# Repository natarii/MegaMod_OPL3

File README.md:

# OPL3 MegaMod
This add-on board lets you play OPL, OPL2, and OPL3 VGM files using your MegaGRRL Desktop.

**This board is provided as an experimental add-on. Software support is working, but incomplete. Software support may improve in the future.**

**MegaGRRL Desktop Firmware v0.97dev or newer is required!** See [Firmware Releases](https://git.agiri.ninja/natalie/megagrrl/-/releases)

## Usage
1. Power off the MegaGRRL Desktop.
2. Remove the YM2612 and SN76489, and seat the addon board into their sockets.
3. Set all 4 DIP switches on the desktop board to OFF.
4. Power on. The presence of the OPL3 board will be detected upon boot. Play an OPL/OPL2/OPL3 VGM file.

## Bill of Materials
| Ref.Dsg. | Value | 
| -------- | ----- |
| C1 | 10uF electrolytic |
| C2 | 47pF ceramic |
| C3 | 2.7nF ceramic |
| C4 | 2.7nF ceramic |
| C5 | 0.1uF ceramic |
| C6 | 0.1uF ceramic |
| C7 | 0.1uF ceramic |
| R1 | 33 ohm |
| R2 | 1k ohm |
| IC1 | YMF262 aka YMF262-M (SMD) |
| IC2 | YAC512 (SMD) |
| IC3 | TL072 (THT) (or SA5532, many opamps will work) |
| D1 | 1N5819 |
| Misc | 0.1" machine pin male-to-male headers, 40 pins total required. Must be machine pin type!!! |

All capacitors, resistors, diode are THT

## Assembly
1. Solder on the SMD components (YMF262, YAC512)
2. Solder on the THT components (SA5532, capacitors, resistors, diode)
3. Solder on the pin headers (use MegaGRRL Desktop IC sockets for alignment)

## Gerber files
Gerbers for JLCPCB are in the `gerbers/` directory.

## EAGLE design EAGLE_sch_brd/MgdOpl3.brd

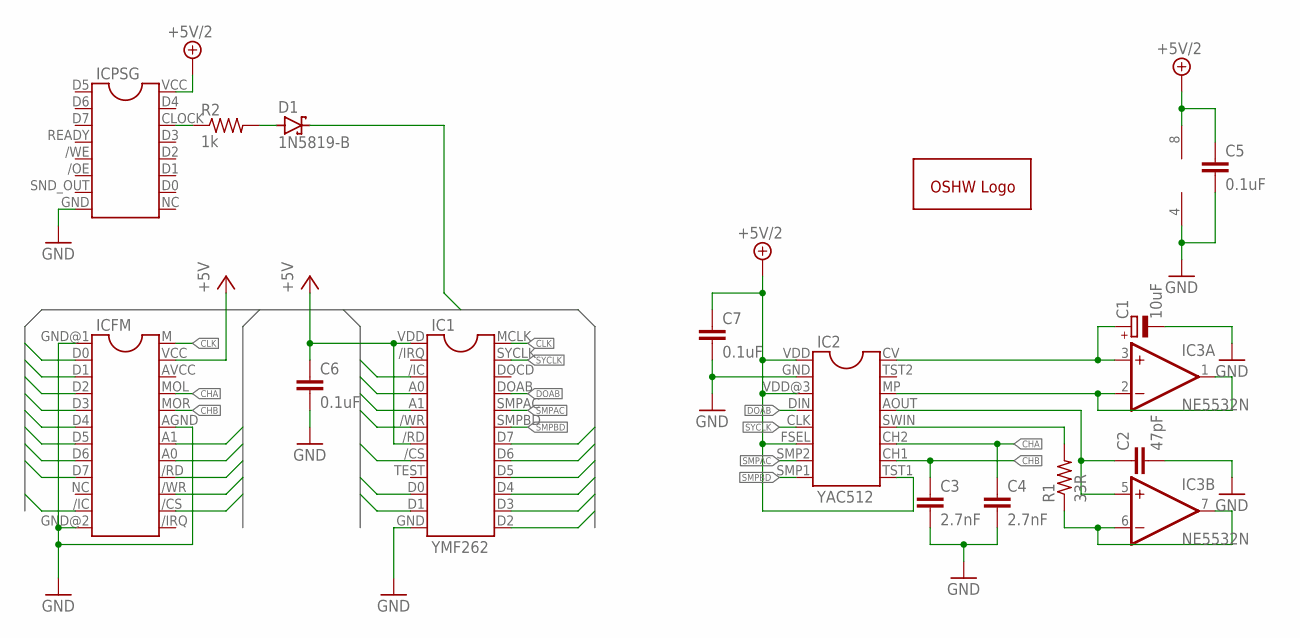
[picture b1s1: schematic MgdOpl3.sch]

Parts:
C1: 10uF; E2,5-5
C2: 47pF; C025-024X044
C3, C4: 2.7nF; C025-024X044
C5, C6, C7: 0.1uF; C025-024X044
D1: 1N5819-B; DO41-7.6
GOLD_ORB_SM2: OSHWLOGOLOGO8MM; OSHW_8MM
IC1: YMF262
IC2: YAC512
IC3: NE5532N; DIL08
ICFM: YM2612YM2612_NOSILK; YM2612_NOSILK
ICPSG: SN76489SN76489_NOSILK; SN76489_NOSILK
R1: 33R; 0204/7
R2: 1k; 0204/7

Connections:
+5V: C6.1, IC1./RD, IC1.VDD, ICFM.VCC
+5V/2: C5.1, C7.1, IC2.FSEL, IC2.TST1, IC2.VDD, IC2.VDD@3 (VDD), IC3.8 (V+), ICPSG.VCC
/CS: IC1./CS, ICFM./CS
/IC: IC1./IC, ICFM./IC
/RD: ICFM./RD
/WR: IC1./WR, ICFM./WR
A0: IC1.A0, ICFM.A0
A1: IC1.A1, ICFM.A1
CHA: C4.1, IC2.CH2, ICFM.MOL
CHB: C3.1, IC2.CH1, ICFM.MOR
CLK: IC1.MCLK, ICFM.M
D0: IC1.D0, ICFM.D0
D1: IC1.D1, ICFM.D1
D2: IC1.D2, ICFM.D2
D3: D1.C, IC1.D3, ICFM.D3
D4: IC1.D4, ICFM.D4
D5: IC1.D5, ICFM.D5
D6: IC1.D6, ICFM.D6
D7: IC1.D7, ICFM.D7
DOAB: IC1.DOAB, IC2.DIN
GND: C1.-, C2.2, C3.2, C4.2, C5.2, C6.2, C7.2, IC1.GND, IC2.GND, IC3.4 (V-), ICFM.AGND, ICFM.GND@1 (GND), ICFM.GND@2 (GND), ICPSG.GND
unnamed: C1.+, IC2.CV, IC3.3 (+IN)
unnamed: IC2.MP, IC3.1 (OUT), IC3.2 (-IN)
unnamed: IC3.6 (-IN), IC3.7 (OUT), R1.1
unnamed: C2.1, IC2.AOUT, IC3.5 (+IN)
unnamed: D1.A, R2.2
unnamed: IC2.SWIN, R1.2
unnamed: ICPSG.CLOCK, R2.1
SMPAC: IC1.SMPAC, IC2.SMP2
SMPBD: IC1.SMPBD, IC2.SMP1
SYCLK: IC1.SYCLK, IC2.CLK

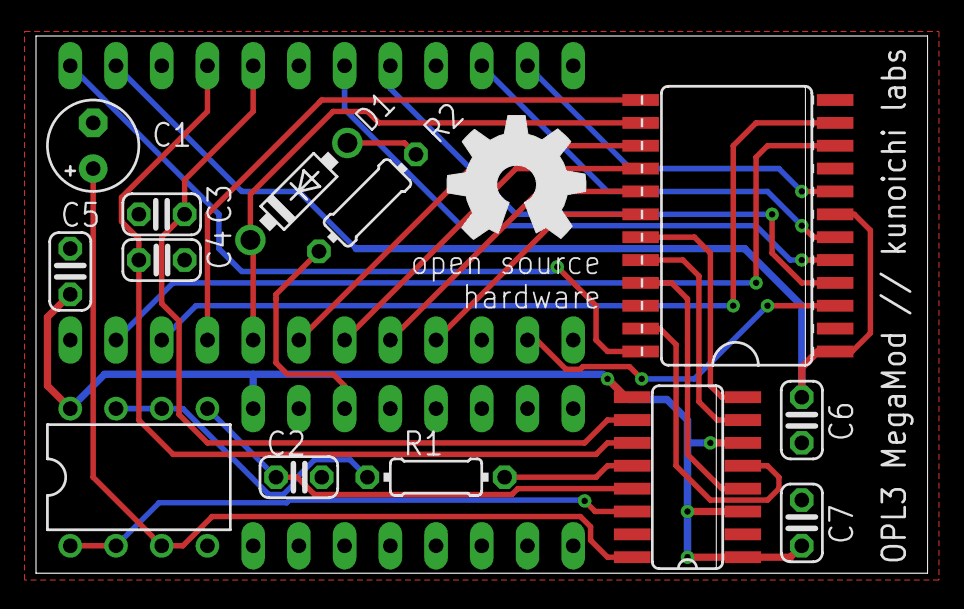
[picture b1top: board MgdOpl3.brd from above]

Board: 2 copper layers, 49.5 x 29.8 mm, 16 parts (0 on the bottom side), 30 nets.

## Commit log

2020-01-01 add basic readme
2020-10-02 add license
2020-10-02 Add image to readme
2020-10-19 Add opamp note
